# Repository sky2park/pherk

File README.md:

# pherk
My DIY keyboard design files. 60% ortholinear and numpad.

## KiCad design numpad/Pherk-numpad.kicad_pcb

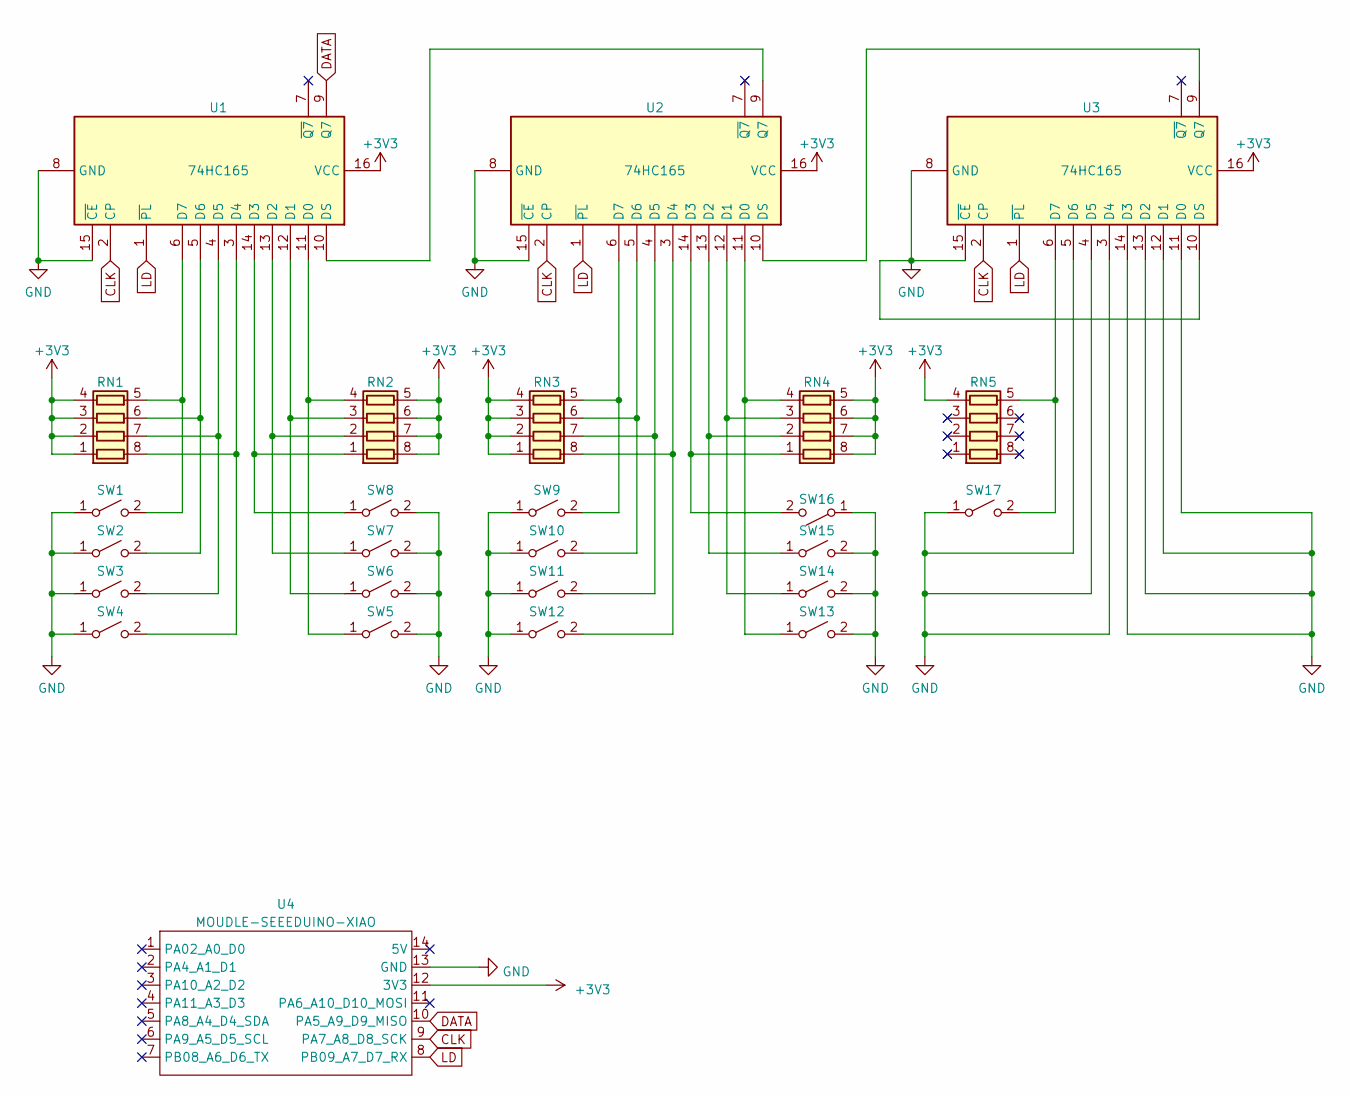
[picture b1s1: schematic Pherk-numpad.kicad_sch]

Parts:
RN1, RN2, RN3, RN4, RN5: R_Pack04; R_Array_Convex_4x0603; LCSC C29718
SW1: SW_SPST; MX-Hotswap-1U; LCSC C5156480
SW2, SW3, SW4, SW5, SW6, SW7, SW8, SW9, SW10, SW11, SW12, SW13, SW16: SW_SPST; MX-Hotswap-1U
SW14, SW15: SW_SPST; MX-Hotswap-2U-Vertical
SW17: SW_SPST; MX-Hotswap-2U-ReversedStabilizers
U1, U2, U3: 74HC165; TSSOP-16_4.4x5mm_P0.65mm; LCSC C80696
U4: MOUDLE-SEEEDUINO-XIAO; rp2040

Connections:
CLK: U1.2 (CP), U2.2 (CP), U3.2 (CP), U4.9 (PA7_A8_D8_SCK)
DATA: U1.9 (Q7), U4.10 (PA5_A9_D9_MISO)
GND: SW1.1 (A), SW2.1 (A), SW3.1 (A), SW4.1 (A), SW5.2 (B), SW6.2 (B), SW7.2 (B), SW8.2 (B), SW9.1 (A), SW10.1 (A), SW11.1 (A), SW12.1 (A), SW13.2 (B), SW14.2 (B), SW15.2 (B), SW16.1 (A), SW17.1 (A), U1.8 (GND), U1.15 (~CE), U2.8 (GND), U2.15 (~CE), U3.3 (D4), U3.4 (D5), U3.5 (D6), U3.8 (GND), U3.10 (DS), U3.11 (D0), U3.12 (D1), U3.13 (D2), U3.14 (D3), U3.15 (~CE), U4.13 (GND)
LD: U1.1 (~PL), U2.1 (~PL), U3.1 (~PL), U4.8 (PB09_A7_D7_RX)
unnamed: RN1.8 (R1.2), SW4.2 (B), U1.3 (D4)
unnamed: RN1.7 (R2.2), SW3.2 (B), U1.4 (D5)
unnamed: RN1.6 (R3.2), SW2.2 (B), U1.5 (D6)
unnamed: RN1.5 (R4.2), SW1.2 (B), U1.6 (D7)
unnamed: RN2.1 (R1.1), SW8.1 (A), U1.14 (D3)
unnamed: RN2.2 (R2.1), SW7.1 (A), U1.13 (D2)
unnamed: RN2.3 (R3.1), SW6.1 (A), U1.12 (D1)
unnamed: RN2.4 (R4.1), SW5.1 (A), U1.11 (D0)
unnamed: RN3.8 (R1.2), SW12.2 (B), U2.3 (D4)
unnamed: RN3.7 (R2.2), SW11.2 (B), U2.4 (D5)
unnamed: RN3.6 (R3.2), SW10.2 (B), U2.5 (D6)
unnamed: RN3.5 (R4.2), SW9.2 (B), U2.6 (D7)
unnamed: RN4.1 (R1.1), SW16.2 (B), U2.14 (D3)
unnamed: RN4.2 (R2.1), SW15.1 (A), U2.13 (D2)
unnamed: RN4.3 (R3.1), SW14.1 (A), U2.12 (D1)
unnamed: RN4.4 (R4.1), SW13.1 (A), U2.11 (D0)
unnamed: RN5.5 (R4.2), SW17.2 (B), U3.6 (D7)
unnamed: U1.10 (DS), U2.9 (Q7)
unnamed: U2.10 (DS), U3.9 (Q7)
VDD: RN1.1 (R1.1), RN1.2 (R2.1), RN1.3 (R3.1), RN1.4 (R4.1), RN2.5 (R4.2), RN2.6 (R3.2), RN2.7 (R2.2), RN2.8 (R1.2), RN3.1 (R1.1), RN3.2 (R2.1), RN3.3 (R3.1), RN3.4 (R4.1), RN4.5 (R4.2), RN4.6 (R3.2), RN4.7 (R2.2), RN4.8 (R1.2), RN5.4 (R4.1), U1.16 (VCC), U2.16 (VCC), U3.16 (VCC), U4.12 (3V3)

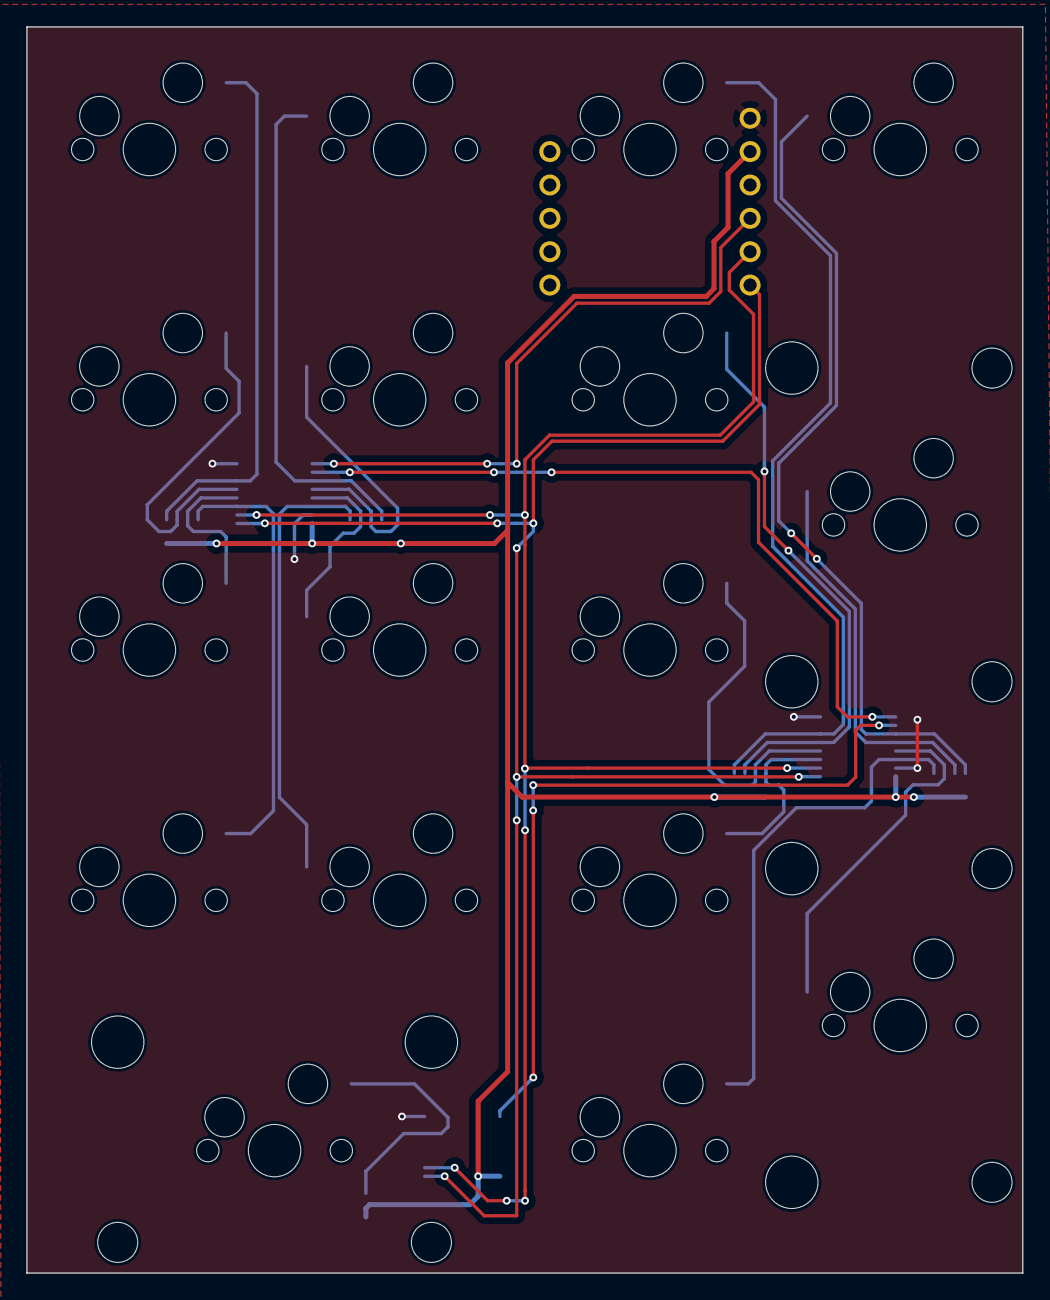
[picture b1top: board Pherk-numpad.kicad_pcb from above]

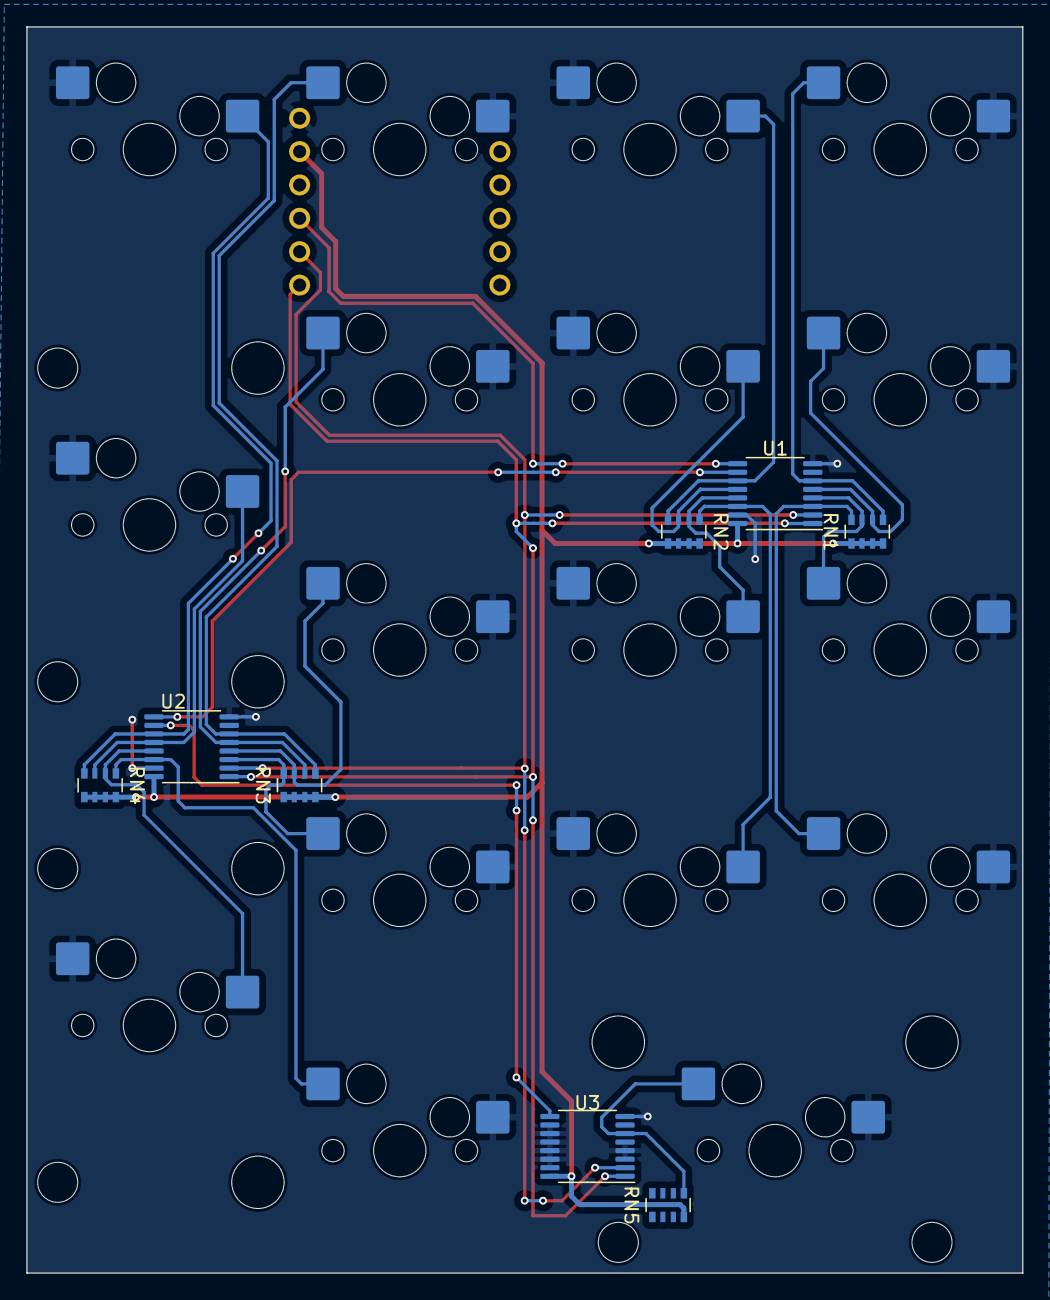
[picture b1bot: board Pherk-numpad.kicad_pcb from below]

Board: 2 copper layers, 75.8 x 94.9 mm, 26 parts (9 on the bottom side), 24 nets.

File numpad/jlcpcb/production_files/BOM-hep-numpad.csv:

Comment,Designator,Footprint,LCSC
R_Pack04,"RN1,RN2,RN3,RN4,RN5",R_Array_Convex_4x0603,C29718
SW_SPST,"SW1,SW10,SW11,SW12,SW13,SW14,SW15,SW16,SW17,SW2,SW3,SW4,SW5,SW6,SW7,SW8,SW9",MX-Hotswap-1U,C5156480
74HC165,"U1,U2,U3",TSSOP-16_4.4x5mm_P0.65mm,C80696

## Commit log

2023-04-11 Add keyboard files
2023-04-11 remove unnessary files
2023-05-28 ortholinear_v2 추가
